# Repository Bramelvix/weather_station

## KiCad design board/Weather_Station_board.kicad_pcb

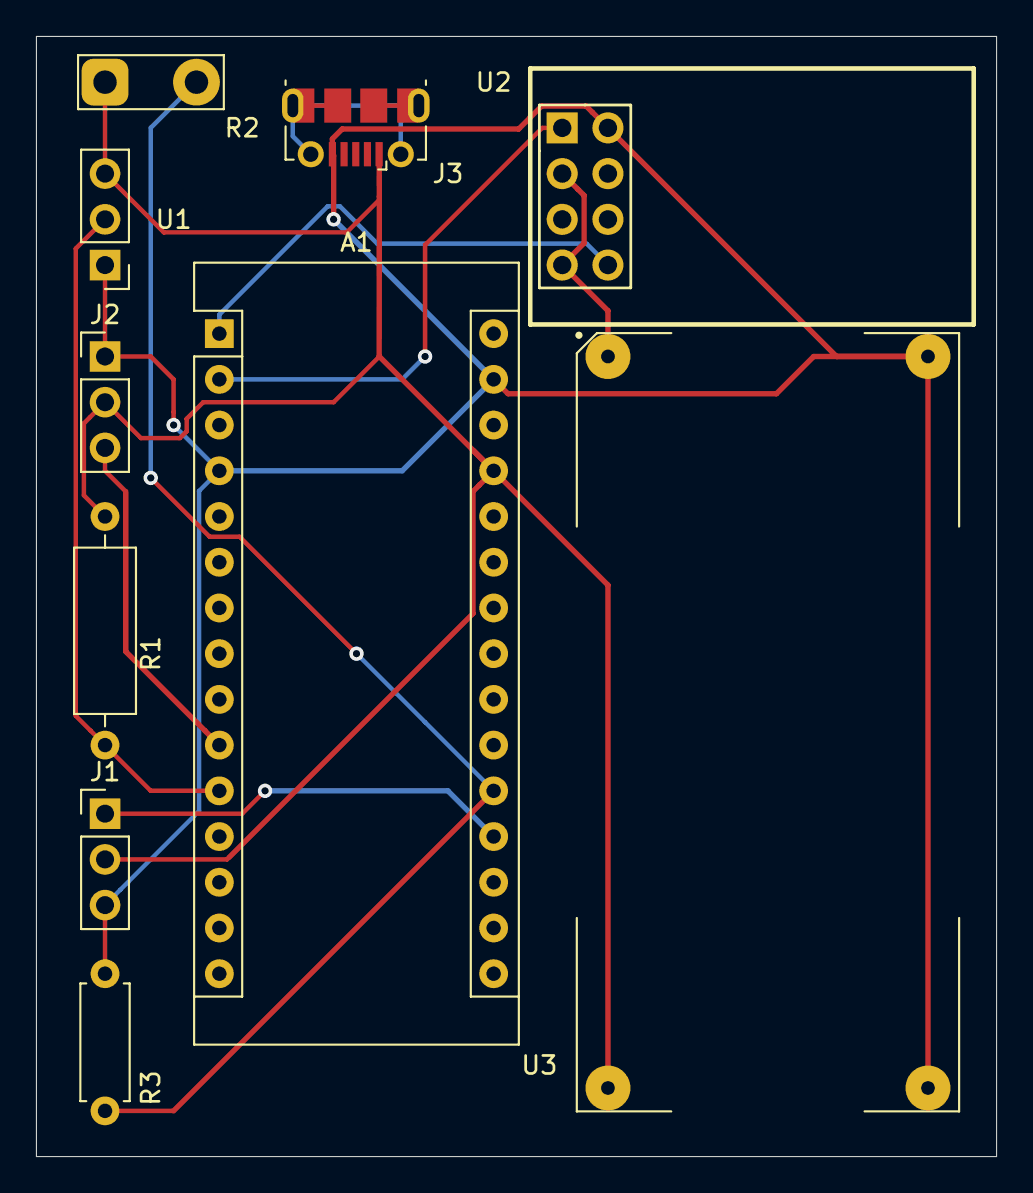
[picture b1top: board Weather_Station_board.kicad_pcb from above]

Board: 2 copper layers, 53.3 x 62.2 mm, 10 parts (0 on the bottom side), 9 nets.

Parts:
A1: Arduino_Nano_v3.x; Arduino_Nano
J1: Soil Moisture; PinHeader_1x03_P2.54mm_Vertical
J2: DHT; PinHeader_1x03_P2.54mm_Vertical
J3: USB_B_Micro; USB_Micro-B_Molex-105017-0001
R1: 4.7k; R_Axial_DIN0309_L9.0mm_D3.2mm_P12.70mm_Horizontal
R2: R_PHOTO; TestPoint_2Pads_Pitch5.08mm_Drill1.3mm
R3: 220; R_Axial_DIN0207_L6.3mm_D2.5mm_P7.62mm_Horizontal
U1: DS18B20; PinHeader_1x03_P2.54mm_Vertical
U2: ESP-01v090; ESP-01
U3: LM2596S-ADJ_module; LM2596module

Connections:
+3V3: U2.3, U2.7, U3.4
+5V: A1.27, J1.2, J2.2, J3.1, R1.1, R2.1, U1.3, U3.1
A0: A1.19, J1.1
A1: A1.20, R2.2, R3.1
D0: A1.2, U2.1
D1: A1.1, U2.8
D7: A1.10, J2.3
D8: A1.11, R1.2, U1.2
GND: A1.4, A1.29, J1.3, J2.1, J3.5, R3.2, U1.1, U2.2, U3.2, U3.3

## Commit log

2020-06-24 Added Api backend
2020-06-24 Ignore unnecessary files
2020-06-25 Renamed dir
2020-07-02 Bump mysql-connector-java from 5.1.44 to 8.0.16 in /backend
    Bumps [mysql-connector-java](https://github.com/mysql/mysql-connector-j) from 5.1.44 to 8.0.16.
    - [Release notes](https://github.com/mysql/mysql-connector-j/releases)
    - [Changelog](https://github.com/mysql/mysql-connector-j/blob/release/8.0/CHANGES)
    - [Commits](https://github.com/mysql/mysql-connector-j/compare/5.1.44...8.0.16)
